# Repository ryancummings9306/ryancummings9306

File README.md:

- 👋 Hi, I’m @ryancummings9306
- 👀 I’m interested in electrical engineering (analog/mixed signals and power electronics)
- 🌱 This is some of my work on the 2023 Texas A&M University Formula Electric SAE car. I am a part of the Battery subteam. 
- 💞️ I’m looking to collaborate on projects that will exercise and expand my knowledge in both high and low voltage circuit design.
- 📫 You may reach me at ryancummings9306@tamu.edu

<!---
ryancummings9306/ryancummings9306 is a ✨ special ✨ repository because its `README.md` (this file) appears on your GitHub profile.
You can click the Preview link to take a look at your changes.
--->

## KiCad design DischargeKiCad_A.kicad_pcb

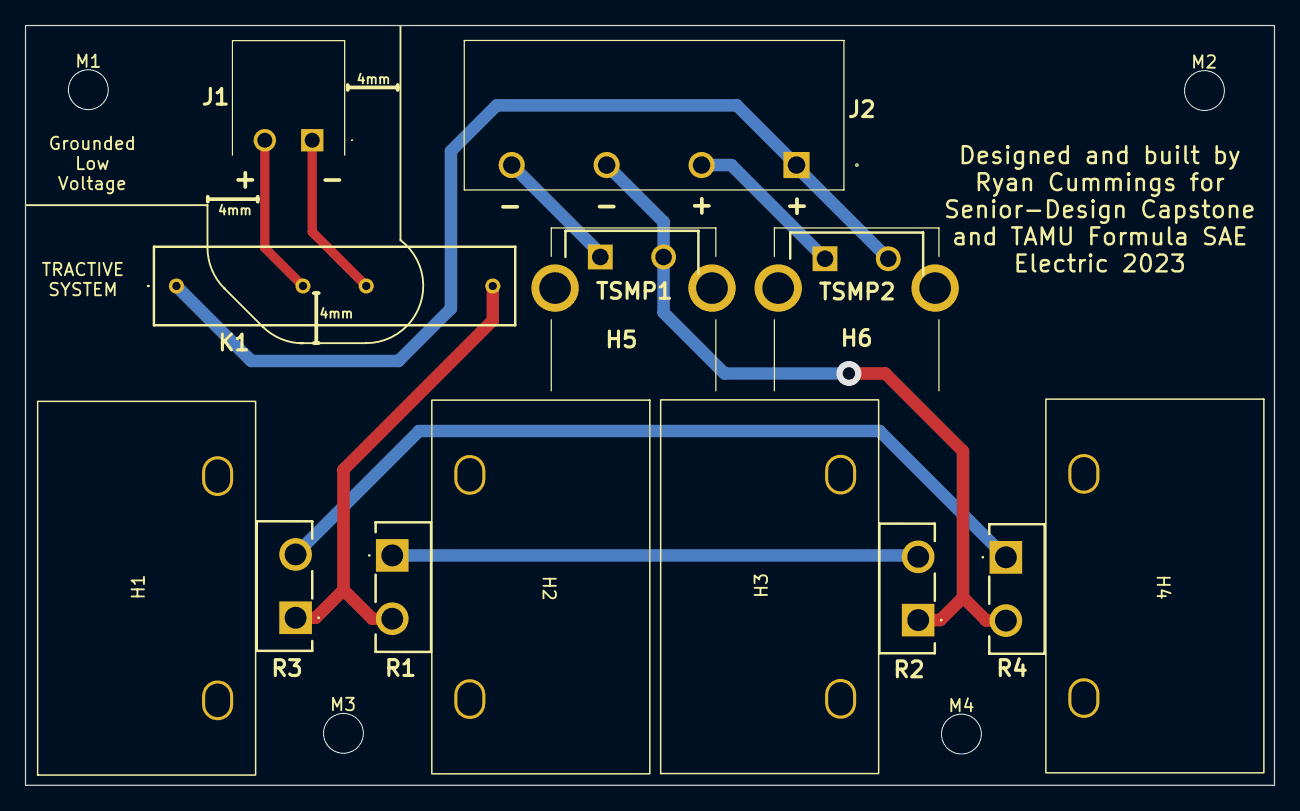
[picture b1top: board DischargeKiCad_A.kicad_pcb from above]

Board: 2 copper layers, 100.3 x 61.0 mm, 19 parts (0 on the bottom side), 9 nets.

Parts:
H1, H2, H3, H4: Heatsink; Heatsink T2X
H5, H6: Heatsink
J1: LV_Connector; LV Conn
J2: TS_Connector; TS Connector
K1: Discharge Relay
M1, M2, M3, M4: MountingHole; MountingHole_3.2mm_M3
R1, R2, R3, R4: MP2060
TSMP1, TSMP2: TSMP

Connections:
unnamed: J1.1, K1.3 (COIL-)
unnamed: J1.2, K1.2 (COIL+)
unnamed: J2.1 (+), K1.1 (COM), TSMP2.2
unnamed: J2.2 (+), TSMP2.1
unnamed: J2.3 (-), R2.1, R4.2, TSMP1.2
unnamed: J2.4 (-), TSMP1.1
unnamed: K1.4 (NC), R1.2, R3.1
unnamed: R1.1, R2.2
unnamed: R3.2, R4.1

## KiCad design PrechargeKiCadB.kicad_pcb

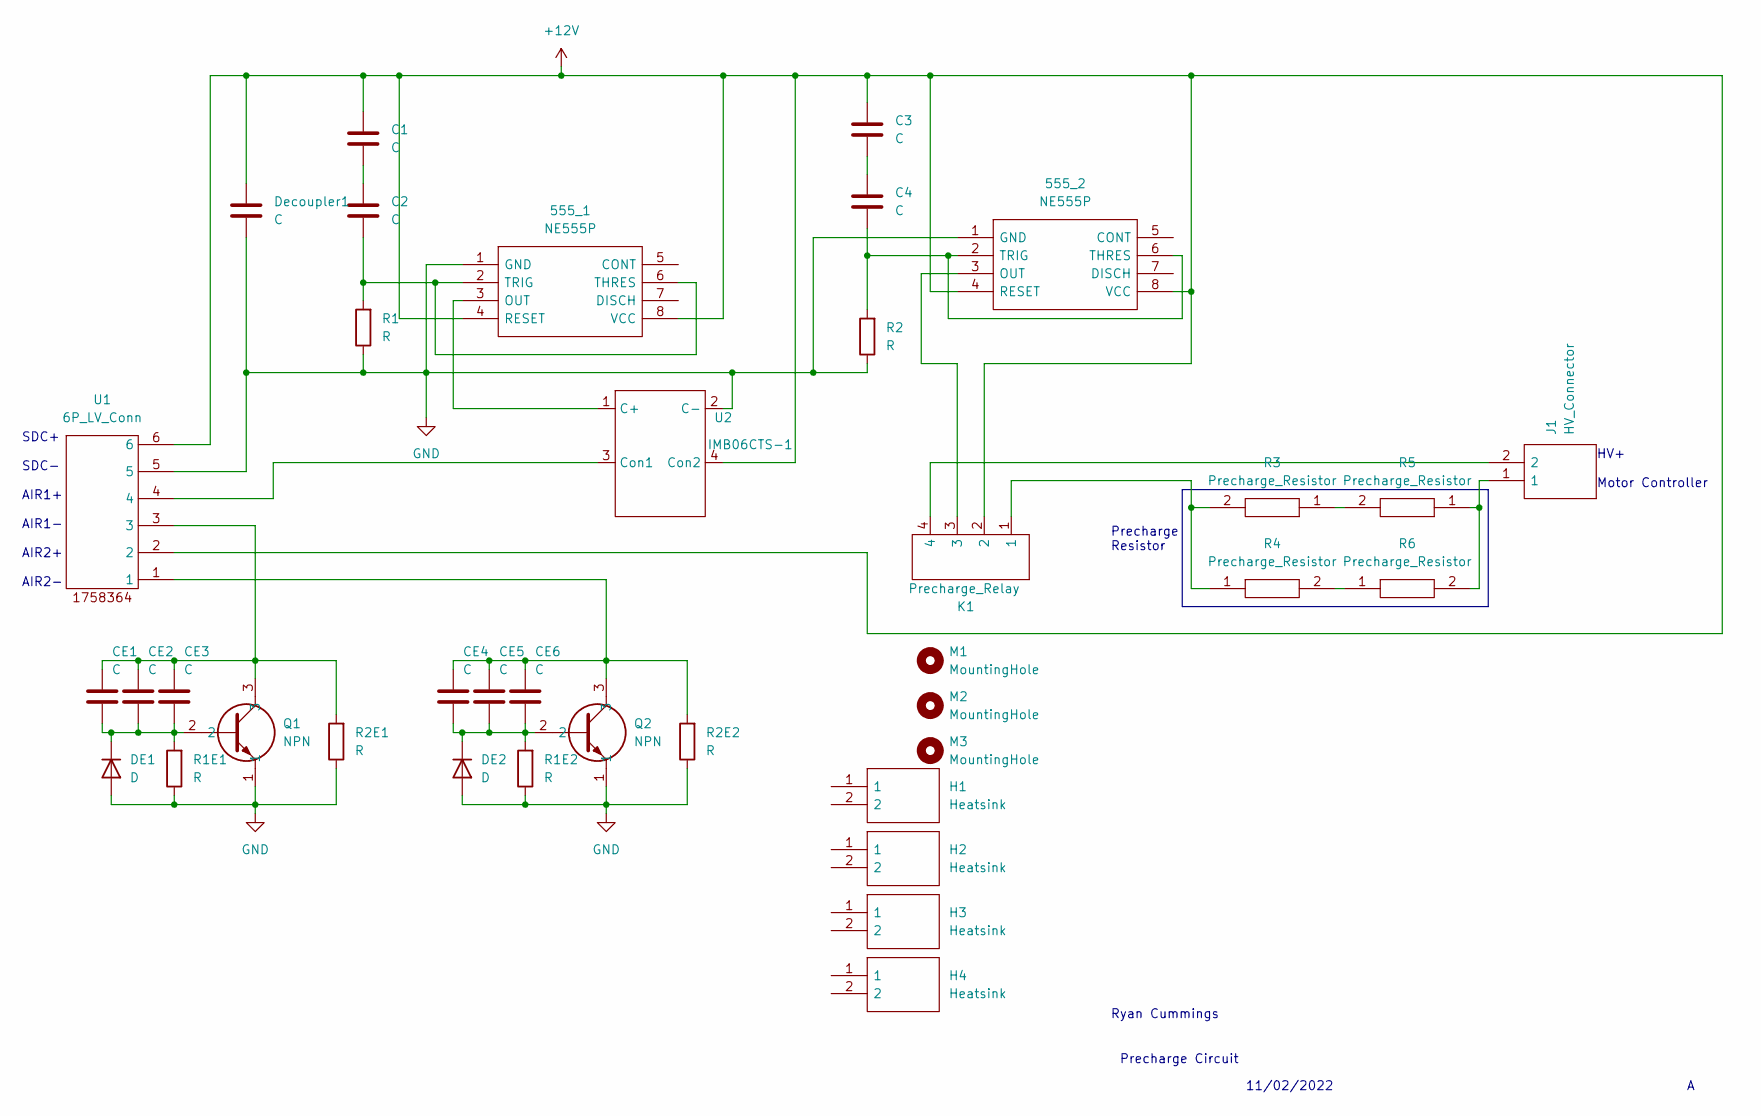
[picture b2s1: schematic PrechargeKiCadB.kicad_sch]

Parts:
555_1, 555_2: NE555P; DIP794W53P254L959H508Q8N; Mouser Part Number 595-NE555P
C1, C2, C3, C4: C; 100u
CE1, CE2, CE3, CE4, CE5, CE6: C; 100uF
DE1, DE2: D; FM4007
Decoupler1: C; C_0805_2012Metric_Pad1.18x1.45mm_HandSolder
H1, H2, H3, H4: Heatsink; Heatsink T2X
J1: HV_Connector; HV_Conn
K1: Precharge_Relay; Precharge Relay
M1, M2, M3: MountingHole; MountingHole_3.2mm_M3
Q1, Q2: NPN
R1, R1E1, R1E2, R2: R; R_1206_3216Metric_Pad1.30x1.75mm_HandSolder
R2E1, R2E2: R; THT Resistor
R3, R4, R5, R6: Precharge_Resistor; Precharge Resistor
U1: 6P_LV_Conn; 6p_LV_Conn
U2: IMB06CTS-1

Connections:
+12V: 555_1.4 (RESET), 555_1.8 (VCC), 555_2.4 (RESET), 555_2.8 (VCC), C1.1, C3.1, Decoupler1.1, K1.2, U1.2, U1.6, U2.4 (Con2)
GND: 555_1.1 (GND), 555_2.1 (GND), DE1.2 (A), DE2.2 (A), Decoupler1.2, Q1.1, Q2.1, R1.1, R1E1.1, R1E2.1, R2.1, R2E1.1, R2E2.1, U1.5, U2.2 (C-)
unnamed: 555_1.2 (TRIG), 555_1.6 (THRES), C2.2, R1.2
unnamed: 555_1.3 (OUT), U2.1 (C+)
unnamed: 555_2.2 (TRIG), 555_2.6 (THRES), C4.2, R2.2
unnamed: 555_2.3 (OUT), K1.3
unnamed: C1.2, C2.1
unnamed: C3.2, C4.1
unnamed: CE1.1, CE2.1, CE3.1, Q1.3, R2E1.2, U1.3
unnamed: CE1.2, CE2.2, CE3.2, DE1.1 (K), Q1.2, R1E1.2
unnamed: CE4.1, CE5.1, CE6.1, Q2.3, R2E2.2, U1.1
unnamed: CE4.2, CE5.2, CE6.2, DE2.1 (K), Q2.2, R1E2.2
unnamed: J1.1, R5.1, R6.2
unnamed: J1.2, K1.4
unnamed: K1.1, R3.2, R4.1
unnamed: R3.1, R5.2
unnamed: R4.2, R6.1
unnamed: U1.4, U2.3 (Con1)

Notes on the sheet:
HV+ Motor Controller
Precharge Resistor
11/02/2022
SDC+ SDC- AIR1+ AIR1- AIR2+ AIR2-
Ryan Cummings
Precharge Circuit

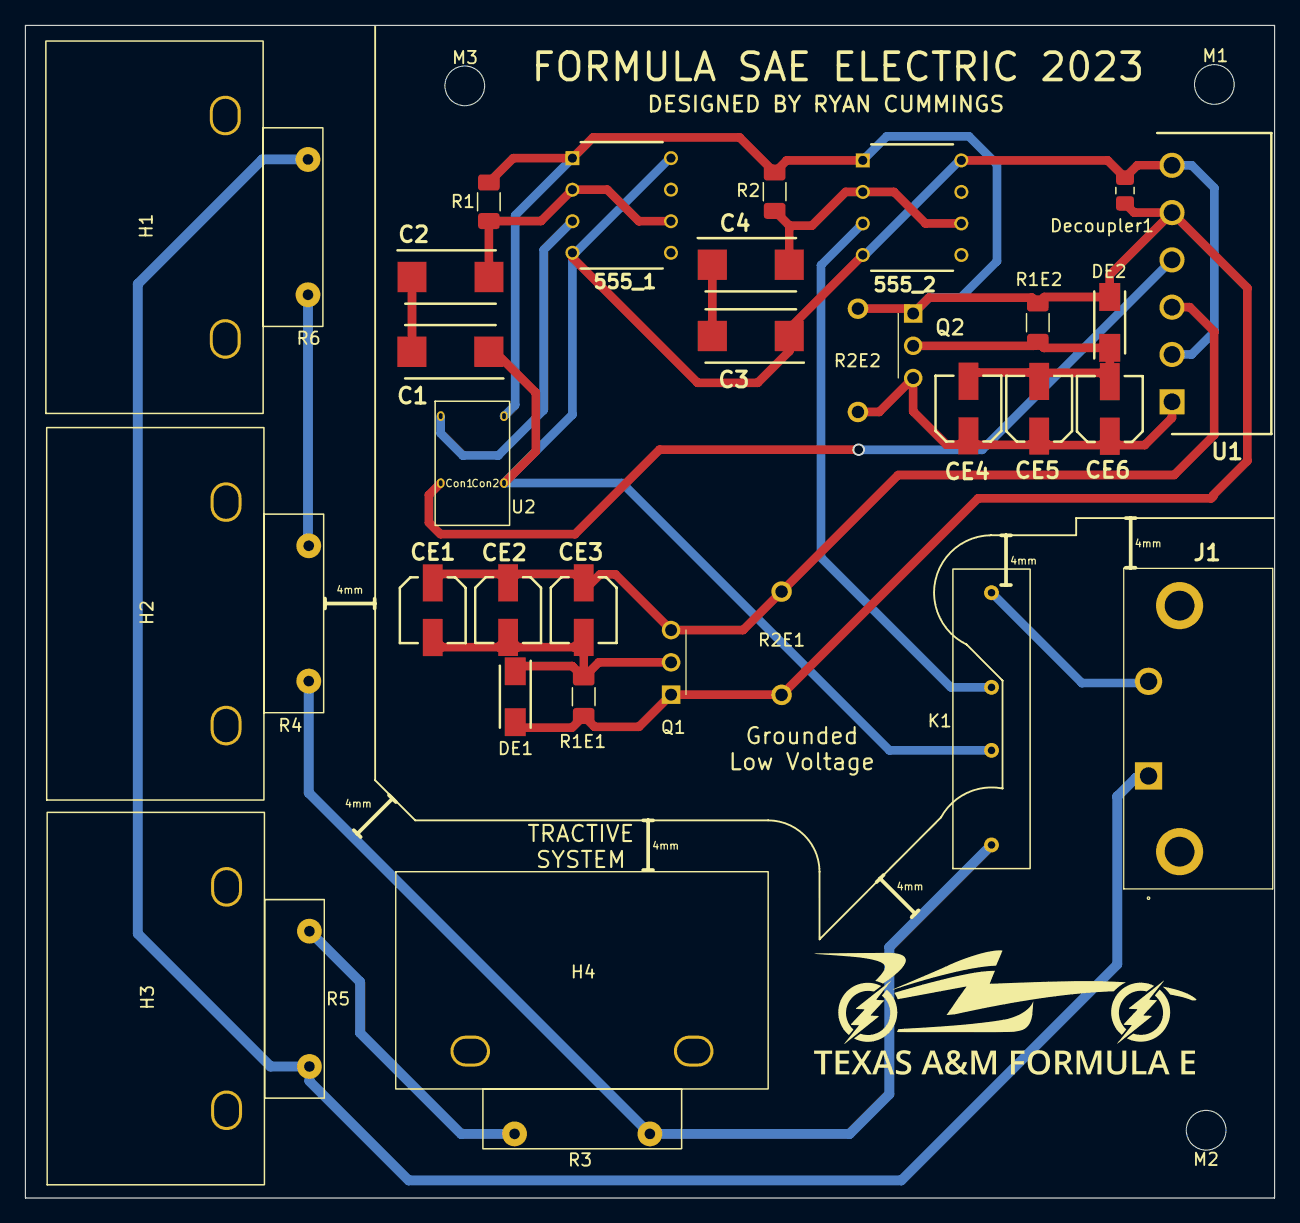
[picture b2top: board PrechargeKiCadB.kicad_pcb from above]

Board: 2 copper layers, 100.6 x 94.5 mm, 38 parts (0 on the bottom side), 18 nets.
